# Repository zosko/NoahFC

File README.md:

# NoahFC
Open Hardware for Smarter Flight

Modular, open-source flight controller with integrated BEC and ESC designs. Build, customize, and fly freely.

#### Based low cost Atmega328 based Flight Controller with necessary features.

# Electronic used
- Flight Controller - [NoahFC](https://github.com/zosko/NoahFC)
- ESC Controller - [NoahESC](https://github.com/zosko/NoahESC)
- BEC - [NoahBEC](https://github.com/zosko/NoahBEC)
- Receiver - (TBS Nano)
- Plane - (ZOHD Drift)
- Camera
- VTX Transmitter

### Features
- [X] **PPM**
- [X] **GPS**
- [X] **Manual mode**
- [X] **Stable mode**
- [X] Return to home
- [X] **OSD**

### Used Pins
Arduino | Component | Arduino | Component
--------|----------|---------|---------
D0| UART RX| D9| Alerons
D1| UART TX| D10 | SS (OSD)
D2| GPS RX | D11 | MOSI (OSD)
D3| PPM Input | D12 | MISO (OSD)
D5| Throttle | D13 | SCK (OSD)
D6| Elevator | SDA | IMU
D8| GPS TX | SCL | IMU

### Transmitter setup
Channel | Info
-----|-----
CH1 | Elevator
CH2 | Alerons
CH3 | Throttle
CH4 | Take off
CH5 | Modes

### Modes
Channel 5 should be 3-position switch
- Min [**Manual**]
- Mid [**Stable**]
- Max [**RTH**]

### Take off
- Channel 4 should be 2-position switch
- Min [**nothing**]
- Max [**Take Off**]

### Firmware
**Download**: [Firmware](firmware.hex)
```
Sketch uses 28472 bytes (92%) of program storage space. Maximum is 30720 bytes.
Global variables use 1267 bytes (61%) of dynamic memory, leaving 781 bytes for local variables. Maximum is 2048 bytes.
```
**Installation**:
`avrdude -p m328 -c arduino -P /dev/ttyUSB0 -b 115200 -F -U flash:w:firmware.hex`

## OSD

## Scheme

## Boards Preview
Board|PCB
---------|---------
|

## Sponsorship

**This project is proudly sponsored by [PCBWay](https://pcbway.com).**

PCBWay specializes in manufacturing high-quality printed circuit boards (PCBs), making them accessible and affordable for both hobbyists and professionals.

Their range of services includes:

- PCB prototyping
- Assembly services
- Instant order quotations
- Expert verification processes
- A user-friendly, hassle-free ordering system

I'm sincerely grateful to PCBWay for their generous support in making this project possible.

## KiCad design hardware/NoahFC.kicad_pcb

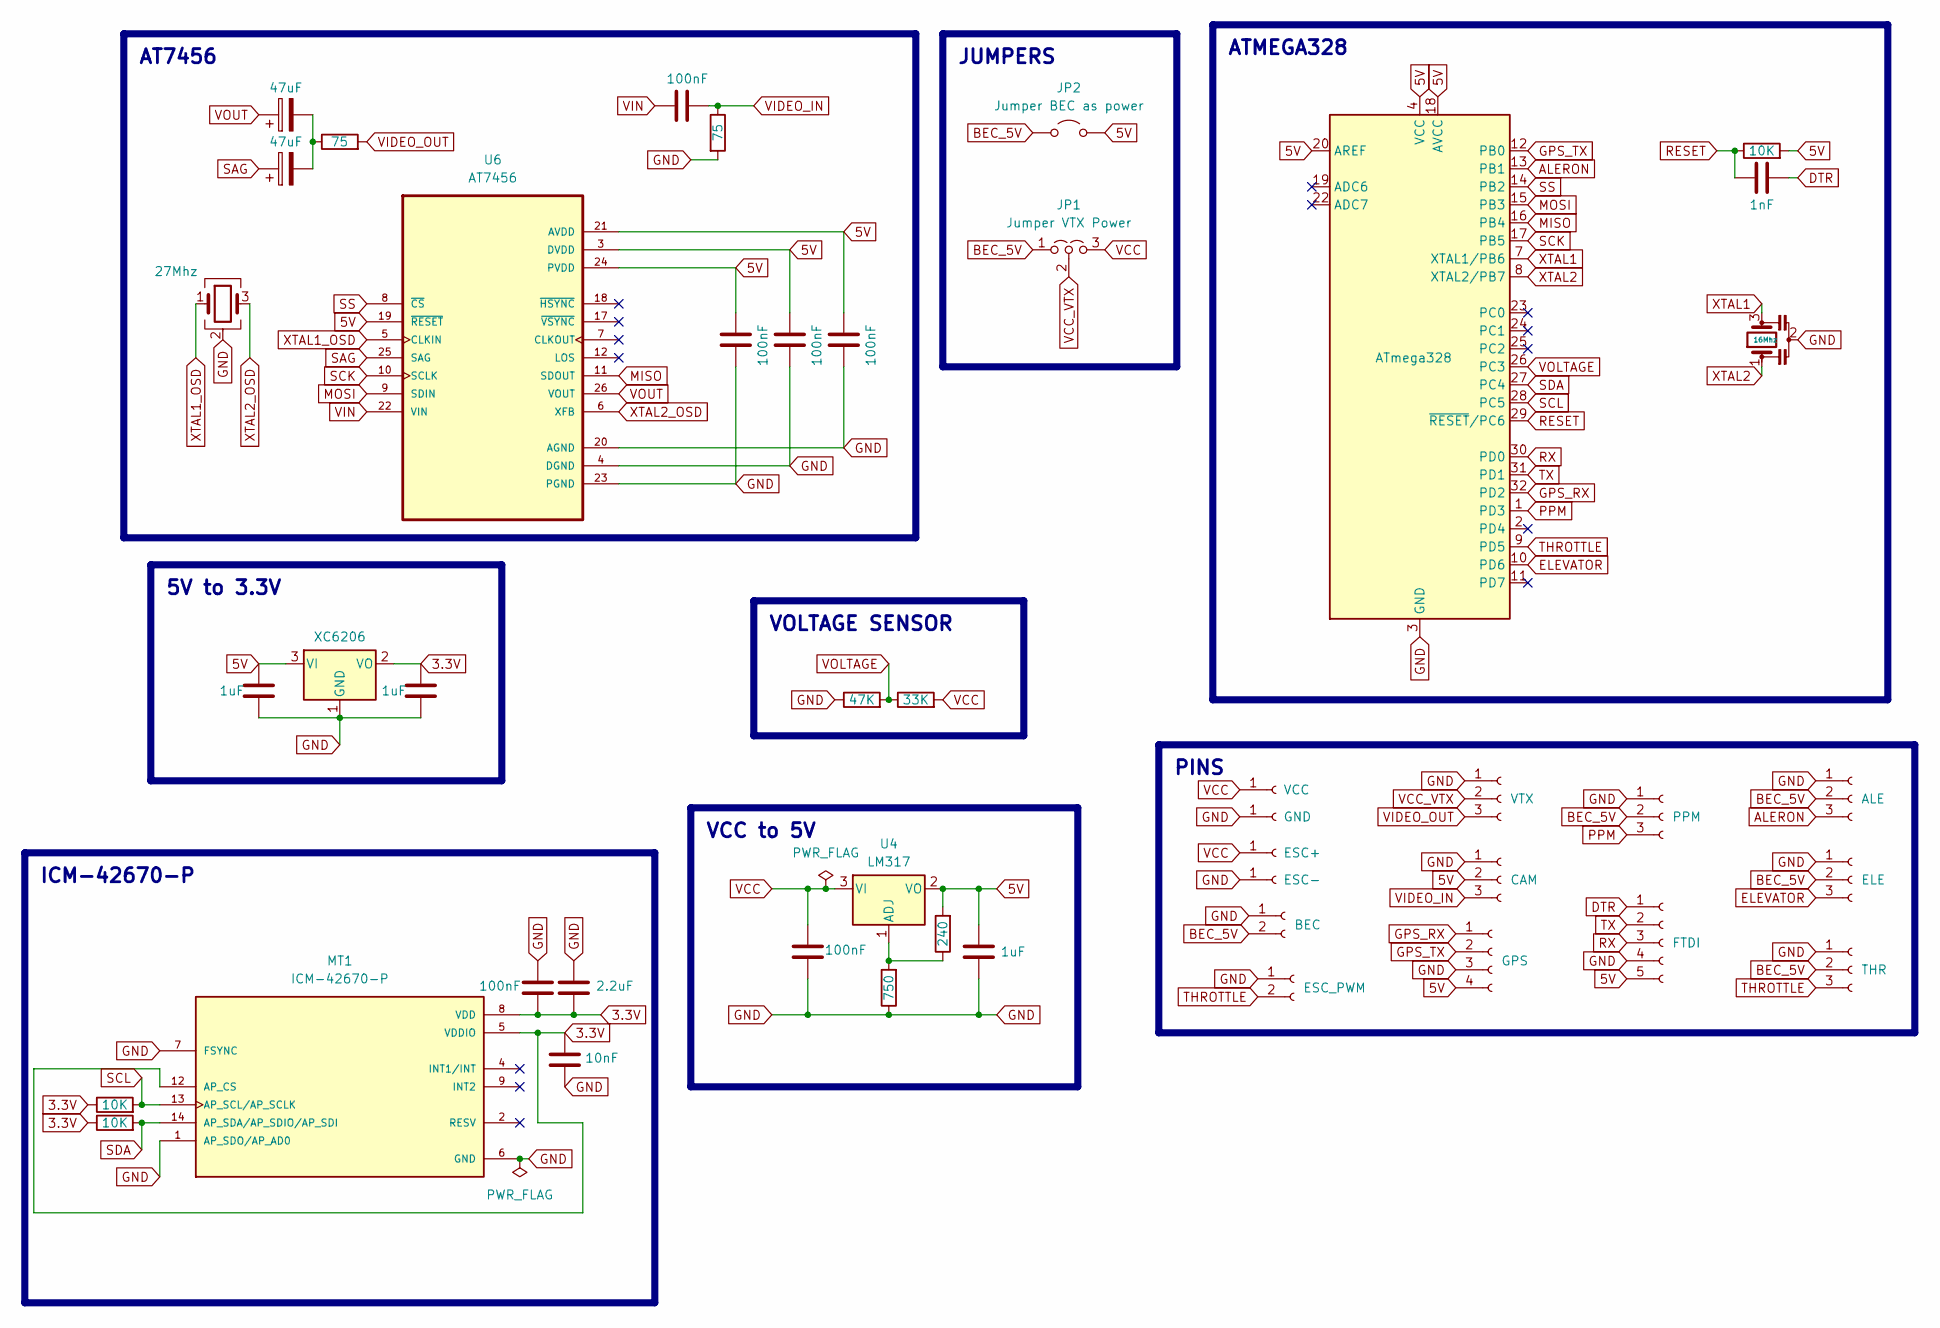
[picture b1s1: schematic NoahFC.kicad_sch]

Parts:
C1, C2, C4, C5, C17: 100nF; C_0805_2012Metric; LCSC C49678
C3: 1nF; C_0805_2012Metric; LCSC C94121
C10, C11, C12: 1uF; C_0805_2012Metric; LCSC C28323
C13: 100nF; C_0805_2012Metric_Pad1.18x1.45mm_HandSolder; LCSC C19186128
C14: 10nF; C_0805_2012Metric_Pad1.18x1.45mm_HandSolder; LCSC C49296944
C15: 2.2uF; C_0805_2012Metric_Pad1.18x1.45mm_HandSolder; LCSC C513763
C18, C19: 47uF; CP_EIA-3216-18_Kemet-A; LCSC C131173
J1: ALE; PinHeader_1x03_P2.54mm_Vertical; LCSC C42431836
J2: ELE; PinHeader_1x03_P2.54mm_Vertical; LCSC C42431836
J3: VCC; TestPoint_Pad_3.0x3.0mm
J4: FTDI; JST_SH_BM05B-SRSS-TB_1x05-1MP_P1.00mm_Vertical; LCSC C160391
J5: GND; TestPoint_Pad_3.0x3.0mm
J6: THR; PinHeader_1x03_P2.54mm_Vertical; LCSC C42431836
J7: PPM; PinHeader_1x03_P2.54mm_Vertical; LCSC C42431836
J8: GPS; JST_SH_BM04B-SRSS-TB_1x04-1MP_P1.00mm_Vertical; LCSC C160390
J9: ESC+; TestPoint_Pad_3.0x3.0mm
J10: ESC-; TestPoint_Pad_3.0x3.0mm
J11: CAM; PinHeader_1x03_P2.54mm_Vertical; LCSC C42431836
J12: VTX; PinHeader_1x03_P2.54mm_Vertical; LCSC C42431836
J15: ESC_PWM; PinHeader_1x02_P2.00mm_Vertical; LCSC C7501607
J17: BEC; PinHeader_1x02_P2.54mm_Vertical; LCSC C42431798
JP1: Jumper VTX Power; SolderJumper-3_P1.3mm_Open_RoundedPad1.0x1.5mm
JP2: Jumper BEC as power; SolderJumper-2_P1.3mm_Open_RoundedPad1.0x1.5mm
MT1: ICM-42670-P; XDCR_ICM-42670-P; LCSC C3288646
R1: 10K; R_0805_2012Metric; LCSC C84376
R2: 240; R_0805_2012Metric; LCSC C17572
R3, R6: 10K; R_0805_2012Metric_Pad1.20x1.40mm_HandSolder; LCSC C84376
R4: 47K; R_0805_2012Metric; LCSC C17713
R5: 33K; R_0805_2012Metric; LCSC C2933415
R9, R10: 75; R_0805_2012Metric; LCSC C2974040
R11: 750; R_0805_2012Metric; LCSC C114546
U1: ATmega328; TQFP-32_7x7mm_P0.8mm; LCSC C618731
U3: XC6206; SOT-23-3; LCSC C3015484
U4: LM317; SOT-223-3_TabPin2; LCSC C68487
U6: AT7456; SOP65P637X110-28N; LCSC C82351
Y1: 16Mhz; Resonator_SMD_Murata_CSTxExxV-3Pin_3.0x1.1mm; LCSC C882606
Y3: 27Mhz; Crystal_SMD_3225-4Pin_3.2x2.5mm; LCSC C5444552

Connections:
3.3V: C11.2, C13.2, C14.1, C15.2, MT1.5 (VDDIO), MT1.8 (VDD), MT1.12 (AP_CS), R3.1, R6.1, U3.2 (VO)
5V: C1.1, C2.1, C4.1, C10.2, C12.2, J4.5, J8.4, J11.2, JP2.2 (B), R1.2, R2.2, U1.4 (VCC), U1.6 (VCC), U1.18 (AVCC), U1.20 (AREF), U3.3 (VI), U4.2 (VO), U6.3 (DVDD), U6.19 (~RESET), U6.21 (AVDD), U6.24 (PVDD)
ALERON: J1.3, U1.13 (PB1)
BEC_5V: J1.2, J2.2, J6.2, J7.2, J17.2, JP1.1 (A), JP2.1 (A)
DTR: C3.2, J4.1
ELEVATOR: J2.3, U1.10 (PD6)
GND: C1.2, C2.2, C4.2, C5.1, C10.1, C11.1, C12.1, C13.1, C14.2, C15.1, J1.1, J2.1, J4.4, J5.1 (Pin_1_1), J6.1, J7.1, J8.3, J10.1 (Pin_1_1), J11.1, J12.1, J15.1, J17.1, MT1.1 (AP_SDO/AP_AD0), MT1.6 (GND), MT1.7 (FSYNC), R4.1, R9.2, R11.1, U1.3 (GND), U1.5 (GND), U1.21 (GND), U3.1 (GND), U6.4 (DGND), U6.20 (AGND), U6.23 (PGND), Y1.2, Y3.2 (G), Y3.4 (G)
GPS_RX: J8.1, U1.32 (PD2)
GPS_TX: J8.2, U1.12 (PB0)
MISO: U1.16 (PB4), U6.11 (SDOUT)
MOSI: U1.15 (PB3), U6.9 (SDIN)
unnamed: C18.2, C19.2, R10.1
unnamed: R2.1, R11.2, U4.1 (ADJ)
PPM: J7.3, U1.1 (PD3)
RESET: C3.1, R1.1, U1.29 (~RESET/PC6)
RX: J4.3, U1.30 (PD0)
SAG: C19.1, U6.25 (SAG)
SCK: U1.17 (PB5), U6.10 (SCLK)
SCL: MT1.13 (AP_SCL/AP_SCLK), R3.2, U1.28 (PC5)
SDA: MT1.14 (AP_SDA/AP_SDIO/AP_SDI), R6.2, U1.27 (PC4)
SS: U1.14 (PB2), U6.8 (~CS)
THROTTLE: J6.3, J15.2, U1.9 (PD5)
TX: J4.2, U1.31 (PD1)
VCC: C5.2, J3.1 (Pin_1_1), J9.1 (Pin_1_1), JP1.3 (B), R5.2, U4.3 (VI)
VCC_VTX: J12.2, JP1.2 (C)
VIDEO_IN: C17.2, J11.3, R9.1
VIDEO_OUT: J12.3, R10.2
VIN: C17.1, U6.22 (VIN)
VOLTAGE: R4.2, R5.1, U1.26 (PC3)
VOUT: C18.1, U6.26 (VOUT)
XTAL1: U1.7 (XTAL1/PB6), Y1.3
XTAL1_OSD: U6.5 (CLKIN), Y3.1
XTAL2: U1.8 (XTAL2/PB7), Y1.1
XTAL2_OSD: U6.6 (XFB), Y3.3

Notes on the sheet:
JUMPERS
ATMEGA328
AT7456
VCC to 5V
5V to 3.3V
VOLTAGE SENSOR
ICM-42670-P
PINS

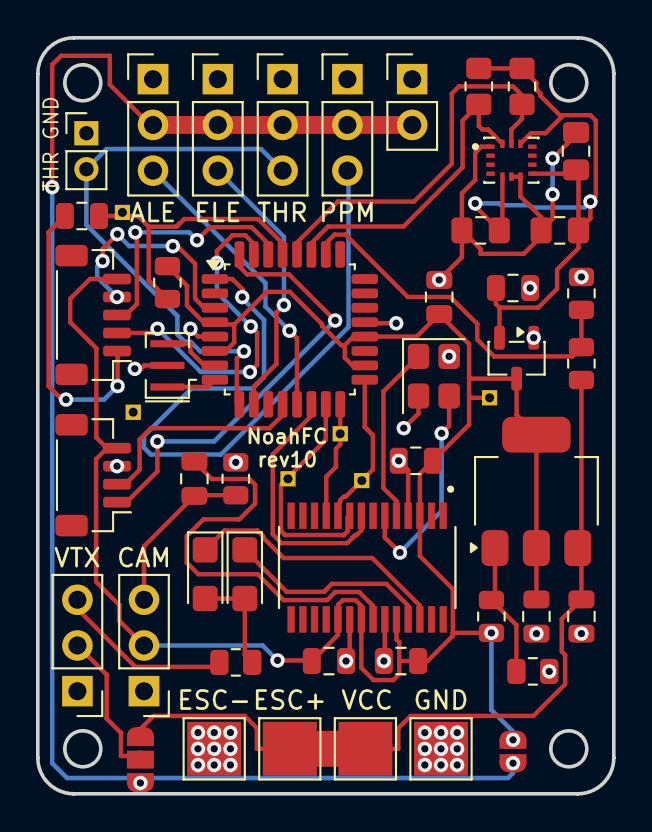
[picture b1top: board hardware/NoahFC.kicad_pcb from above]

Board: 2 copper layers, 32.0 x 42.0 mm, 46 parts (0 on the bottom side), 34 nets.

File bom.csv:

"Reference","Value","Qty","LCSC"
"C1,C2,C4,C5,C13,C17","100nF","6","C19186128,C49678"
"C3","1nF","1","C94121"
"C10,C11,C12","1uF","3","C28323"
"C14","10nF","1","C49296944"
"C15","2.2uF","1","C513763"
"C18,C19","47uF","2","C131173"
"J1","ALE","1","C42431836"
"J2","ELE","1","C42431836"
"J3","VCC","1",""
"J4","FTDI","1","C160391"
"J5","GND","1",""
"J6","THR","1","C42431836"
"J7","PPM","1","C42431836"
"J8","GPS","1","C160390"
"J9","ESC+","1",""
"J10","ESC-","1",""
"J11","CAM","1","C42431836"
"J12","VTX","1","C42431836"
"J15","ESC_PWM","1","C7501607"
"J17","BEC","1","C42431798"
"JP2","Jumper BEC as power","1",""
"MT1","ICM-42670-P","1","C3288646"
"R1,R3,R6","10K","3","C84376"
"R2","240","1","C17572"
"R4","47K","1","C17713"
"R5","33K","1","C2933415"
"R9,R10","75","2","C2974040"
"R11","750","1","C114546"
"U1","ATmega328","1","C618731"
"U3","XC6206","1","C3015484"
"U4","LM317","1","C68487"
"U6","AT7456","1","C82351"
"Y1","16Mhz","1","C882606"
"Y3","27Mhz","1","C5444552"

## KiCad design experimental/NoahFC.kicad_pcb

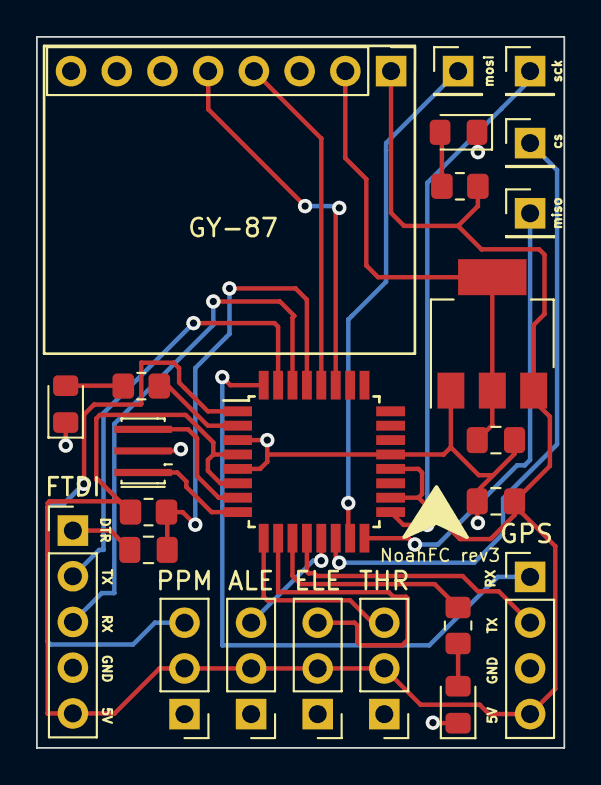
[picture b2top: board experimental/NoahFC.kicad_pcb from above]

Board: 2 copper layers, 29.3 x 39.5 mm, 24 parts (0 on the bottom side), 26 nets.

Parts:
C3: 1nF; C_0805_2012Metric_Pad1.18x1.45mm_HandSolder
C10: 10uF; C_0805_2012Metric_Pad1.18x1.45mm_HandSolder
C11: 22uF; C_0805_2012Metric_Pad1.18x1.45mm_HandSolder
D1: GPS; LED_0805_2012Metric_Pad1.15x1.40mm_HandSolder
D2: MODE; LED_0805_2012Metric_Pad1.15x1.40mm_HandSolder
D3: PWR; LED_0805_2012Metric_Pad1.15x1.40mm_HandSolder
GPS: GPS; PinHeader_1x04_P2.54mm_Vertical
J1: ALE; PinHeader_1x03_P2.54mm_Vertical
J2: ELE; PinHeader_1x03_P2.54mm_Vertical
J3: GY-87; PinHeader_1x08_P2.54mm_Vertical
J4: FTDI; PinHeader_1x05_P2.54mm_Vertical
J6: THR; PinHeader_1x03_P2.54mm_Vertical
J7: PPM; PinHeader_1x03_P2.54mm_Vertical
R1: 10K; R_0805_2012Metric_Pad1.20x1.40mm_HandSolder
R2, R3, R4: 330; R_0805_2012Metric_Pad1.20x1.40mm_HandSolder
U1: ATmega328; TQFP-32_7x7mm_P0.8mm
U4: AMS1117-3.3; SOT-223-3_TabPin2
Y1: 16Mhz; Resonator_SMD_Murata_CSTxExxV-3Pin_3.0x1.1mm_HandSoldering
cs: CS; PinHeader_1x01_P2.54mm_Vertical
miso: MISO; PinHeader_1x01_P2.54mm_Vertical
mosi: MOSI; PinHeader_1x01_P2.54mm_Vertical
sck: SCK; PinHeader_1x01_P2.54mm_Vertical

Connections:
3.3V: C11.2, J3.2, U4.2 (VO)
5V: C10.2, GPS.4, J1.2, J2.2, J3.1, J4.5, J6.2, J7.2, R1.2, R4.1, U1.4 (VCC), U1.6 (VCC), U1.18 (AVCC), U1.20 (AREF), U4.3 (VI)
ALERON: J1.3, U1.13 (PB1)
CS: U1.14 (PB2), cs.1
DTR: C3.2, J4.1
ELEVATOR: J2.3, U1.10 (PD6)
GND: C10.1, C11.1, D1.1 (K), D2.1 (K), D3.1 (K), GPS.3, J1.1, J2.1, J3.3, J4.4, J6.1, J7.1, U1.3 (GND), U1.5 (GND), U1.21 (GND), U4.1 (GND), Y1.2
GPS_RX: GPS.1, U1.32 (PD2)
GPS_TX: GPS.2, U1.12 (PB0)
LED_GPS: R2.1, U1.11 (PD7)
LED_MODE: R3.1, U1.2 (PD4)
MISO: U1.16 (PB4), miso.1
MOSI: U1.15 (PB3), mosi.1
unnamed: D1.2 (A), R2.2
unnamed: D2.2 (A), R3.2
unnamed: D3.2 (A), R4.2
PPM: J7.3, U1.1 (PD3)
RESET: C3.1, R1.1, U1.29 (~RESET/PC6)
RX: J4.3, U1.30 (PD0)
SCK: U1.17 (PB5), sck.1
SCL: J3.4, U1.28 (PC5)
SDA: J3.5, U1.27 (PC4)
THROTTLE: J6.3, U1.9 (PD5)
TX: J4.2, U1.31 (PD1)
XTAL1: U1.7 (XTAL1/PB6), Y1.3
XTAL2: U1.8 (XTAL2/PB7), Y1.1

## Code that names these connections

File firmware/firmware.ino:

#include <Wire.h>
#include <NMEAGPS.h>
#include <GPSport.h>
#include <Streamers.h>
#include <PPMReader.h>
#include <ServoTimer2.h>
#include <SimpleKalmanFilter.h>

//#include <SPI.h>
//#include <max7456.h>

// OSD
//Max7456 osd;

// SERVOS
const int PIN_ALERON = 9;
const int PIN_ELEVATOR = 10;
const int PIN_THROTTLE = 11;
ServoTimer2 servoThrottle;
ServoTimer2 servoElevator;
ServoTimer2 servoAleron;

//MPU6050
int pitchAngle = 0;
int rollAngle = 0;
SimpleKalmanFilter kalmanPitch(10, 10, 0.01);
SimpleKalmanFilter kalmanRoll(10, 10, 0.01);

float Cal_GyX, Cal_GyY, Cal_GyZ;
float xAngle, yAngle, zAngle;
const float alpha = 0.96;

//HMC5883L
int headingDegrees = 0;

// PPM
const int PIN_PPM =  3;
PPMReader ppm(PIN_PPM, 5); // (InterruptPin, MaxChannels)
unsigned int ch1 = 1500;
unsigned int ch2 = 1500;
unsigned int ch3 = 1500;
unsigned int ch4 = 1500;
unsigned int ch5 = 1500;

// VOLTAGE READ
float voltage = 0.0;
const int PIN_VOLTAGE = A2;

// LEDS
const int PIN_LED_MODE = 4;
const int PIN_LED_GPS = 5;
const int PIN_LED_POWER = 7;

// GPS
enum navigation_turn {
  DO_NOTHING,
  ARRIVED,
  FORWARD,
  TURN_LEFT,
  TURN_RIGHT,
  TURN_LITTLE_LEFT,
  TURN_LITTLE_RIGHT,
  TURN_AROUND
};
navigation_turn navigation;
NeoGPS::Location_t homeLocation;
static NMEAGPS gps;
gps_fix fix;

int nav_dir = 0;

// LoopTimer
long loop_timer;

void setup() {
  //  SPI.begin();
  Wire.begin();

  pinMode(PIN_VOLTAGE, INPUT);
  pinMode(PIN_LED_MODE, OUTPUT);
  pinMode(PIN_LED_GPS, OUTPUT);
  pinMode(PIN_LED_POWER, OUTPUT);

  servoAleron.attach(PIN_ALERON);
  servoElevator.attach(PIN_ELEVATOR);
  servoThrottle.attach(PIN_THROTTLE);

  gpsPort.attachInterrupt(GPSisr);
  gpsPort.begin(9600);

  ppm.channelValueMaxError = 100; // trashhold PPM for min / max
  ppm.blankTime = 2200;

  loop_timer = micros();

  setupOSD();
  setupMPU6050();
  setupHMC5883L();
  ledStartup();
}

void loop() {
  readPPM();
  readGPS();
  readMPU();
  readHMC5883L();
  readVoltage();
  showOSD_Data();

  if (ch5 < 1300) { // Manual
    pitchAngle = 0;
    rollAngle = 0;
    ledManualMode();
  } else if (ch5 > 1700) { // Return to land
    ch1 = 0;
    ch2 = 0;
    ch3 = 1030;

    switch (navigation) {
      case DO_NOTHING:
        break;
      case ARRIVED:
        ch1 = 2000;
        break;
      case FORWARD:
        break;
      case TURN_LEFT:
        ch1 = 1200;
        break;
      case TURN_RIGHT:
        ch1 = 1800;
        break;
      case TURN_LITTLE_LEFT:
        ch1 = 1300;
        break;
      case TURN_LITTLE_RIGHT:
        ch1 = 1600;
        break;
      case TURN_AROUND:
        ch1 = 2000;
        break;
    }

    navigation = DO_NOTHING;

    ledAngleMode();
  } else { // Angle Mode
    ledAngleMode();
  }

  pitchAngle = kalmanPitch.updateEstimate(pitchAngle);
  rollAngle = kalmanRoll.updateEstimate(rollAngle);

  servoAleron.write(pitchAngle + ch1);
  servoElevator.write(rollAngle + ch2);
  servoThrottle.write(ch3);

  while (micros() - loop_timer < 4000);  //Wait until the loop_timer reaches 4000us (250Hz) before starting the next loop
  loop_timer = micros();
}

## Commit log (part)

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2022-04-13 separate panel board
2022-04-13 initial code
2022-05-07 setup code
2022-05-07 revision 1
2022-05-13 add components for gps, ppm, stabilization
2022-05-13 firmware
2022-05-13 Add library used
2022-05-17 add components
2022-05-17 pin mapping
2022-05-19 remove one aleron servo
2022-05-19 vanish components code
2022-05-19 rev1 code
2022-05-19 include servoTimer
2022-05-19 implement #define for DEBUG
2022-05-27 route board
2022-05-28 rev1 images
2022-05-28 rev1 updates
2022-05-28 design improve
2022-05-28 pin improve
2022-05-29 mapping pins
2022-05-30 fill board
2022-06-30 gps pin correction
2022-06-30 include failsafe
2022-06-30 add voltage in debug
2022-06-30 add leds funcs
2022-06-30 add correction in voltage read
2022-06-30 improve navigation
2022-06-30 add RESET pad
2022-06-30 enumarate navigation
2022-06-30 simple try
2022-07-27 add rev2 version board
2022-07-27 add scheme
2022-07-29 add max7456 library
2022-07-29 update firmware to include osd and compass
2022-07-29 add board rev2 image
2022-07-29 update scheme / design and board
2022-07-30 update pins
2022-07-30 add new images
2022-07-30 redesign board
2022-07-30 remove panel
2022-07-30 new scheme
2022-08-03 tidy board
2022-08-03 add azumuth
2022-08-08 add PIDs
2022-08-08 osd tidy
2022-08-08 rename folder
2022-08-20 general improvements in stable flight
2022-08-20 kalman filter
2022-08-21 remove debug remove mpu offest
2022-08-21 route rev2
2022-10-01 small tidy in firmware
2022-10-12 reduce
2022-11-03 description
2022-12-22 add experimental revision
2022-12-22 add images
2023-09-07 scheme rev4
2023-09-07 images for rev4
2023-09-07 rev4 project
2023-09-07 image resize
2023-09-28 removed experimental version
2023-09-28 add bottom labels
2023-09-28 add firmware
2023-09-28 Add LICENSE
2023-10-29 new firmware
2023-11-14 add rev5 scheme
2023-11-14 update project rev5
2023-11-14 remove unused library
2023-11-14 add step file for xc6206
2023-11-19 edit footprint
2023-11-19 add sda scl pinout
2023-11-28 add jumper, organize pcb
2023-11-28 rev5 scheme with jumper
2023-11-28 new images with organized pcb with jumper
2023-11-30 gerbers path
2024-02-28 update to kicad 8
2024-03-05 rev6 project
2024-03-05 scheme for rev6
2024-03-05 add missing board file
2024-04-20 reworked rev6 - experimental
2024-07-03 pixelization of dimensions
2024-07-06 add silk
2024-07-06 proj file update
2024-07-29 replace buck converter with LM317
2025-07-31 remove scheme file
2025-07-31 rework hardware libraries
2025-07-31 update to rev7 board
2025-08-01 remove unused pin
2025-09-11 add sponsor
2025-10-24 updates for rev7
2025-10-25 increaes line
2025-11-30 add bom file
2025-11-30 add new firmware for rev7
2025-11-30 update project with LCSC parts, fix some component prepare rev8
2025-12-21 added 5V jumper for BEC
2026-01-02 add git ignore
2026-04-07 add jumpers for vtx
